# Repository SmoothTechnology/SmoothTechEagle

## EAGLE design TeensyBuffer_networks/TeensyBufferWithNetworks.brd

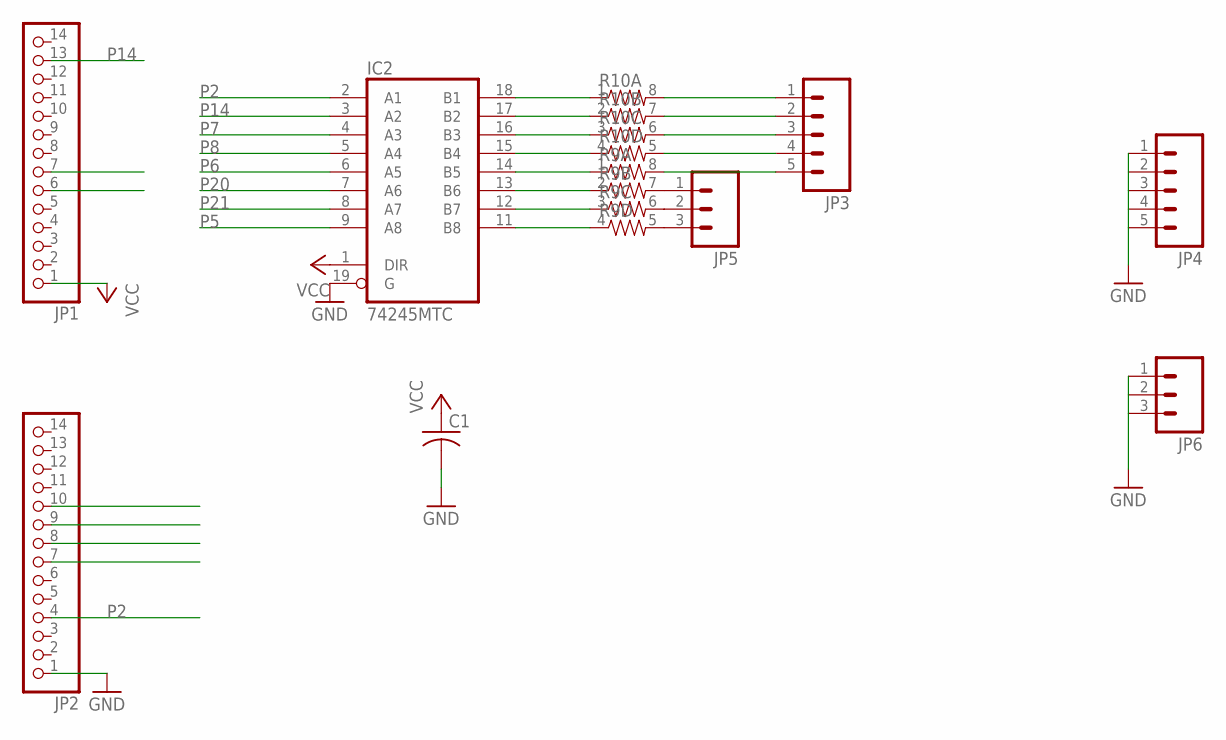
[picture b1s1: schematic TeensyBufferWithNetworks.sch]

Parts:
C1: C-USC0805; C0805
IC2: 74245MTC; SSOP20
JP1, JP2: PINHD-1X14-CB; 1X14-CB
JP3, JP4: M05NO_SILK; 1X05_NO_SILK
JP5, JP6: M031X03_NO_SILK; 1X03_NO_SILK
R9, R10: RESISTOR-ARRAY0603-ARV; 0603-ARV

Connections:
GND: C1.2, IC2.10 (GND), IC2.19 (G), JP2.1, JP4.1, JP4.2, JP4.3, JP4.4, JP4.5, JP6.1, JP6.2, JP6.3
unnamed: JP5.1, R9.7 (2)
unnamed: JP5.2, R9.6 (2)
unnamed: IC2.18 (B1), R10.1
unnamed: IC2.17 (B2), R10.2 (1)
unnamed: IC2.16 (B3), R10.3 (1)
unnamed: IC2.15 (B4), R10.4 (1)
unnamed: IC2.14 (B5), R9.1
unnamed: IC2.13 (B6), R9.2 (1)
unnamed: IC2.12 (B7), R9.3 (1)
unnamed: IC2.11 (B8), R9.4 (1)
unnamed: JP5.3, R9.5 (2)
unnamed: JP3.1, R10.8 (2)
unnamed: JP3.2, R10.7 (2)
unnamed: JP3.3, R10.6 (2)
unnamed: JP3.4, R10.5 (2)
unnamed: JP3.5, R9.8 (2)
P2: IC2.2 (A1), JP2.4
P5: IC2.9 (A8), JP2.7
P6: IC2.6 (A5), JP2.8
P7: IC2.4 (A3), JP2.9
P8: IC2.5 (A4), JP2.10
P14: IC2.3 (A2), JP1.13
P20: IC2.7 (A6), JP1.7
P21: IC2.8 (A7), JP1.6
VCC: C1.1, IC2.1 (DIR), IC2.20 (VCC), JP1.1

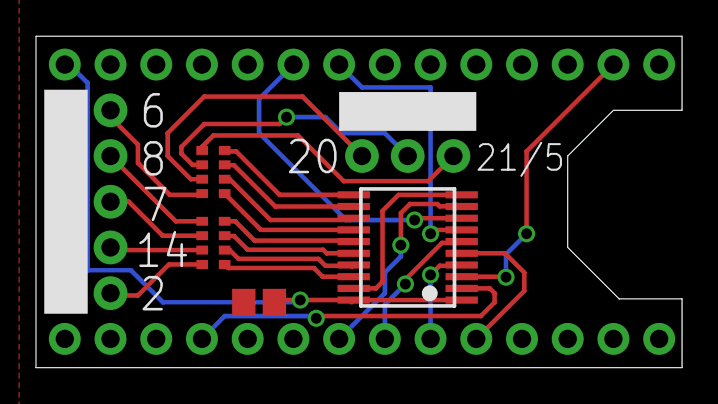
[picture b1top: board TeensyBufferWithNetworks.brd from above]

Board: 2 copper layers, 35.9 x 18.4 mm, 10 parts (0 on the bottom side), 26 nets.

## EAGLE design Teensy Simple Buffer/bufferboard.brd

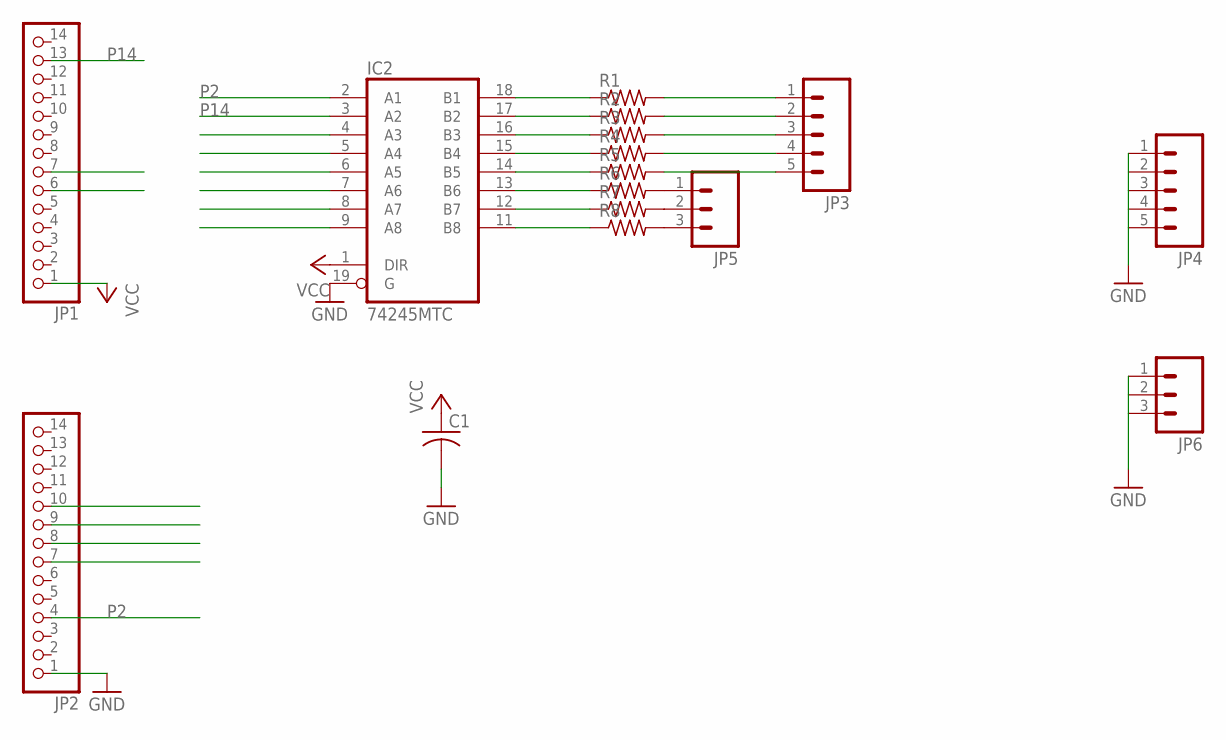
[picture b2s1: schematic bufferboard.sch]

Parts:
C1: C-USC0805; C0805
IC2: 74245MTC; SSOP20
JP1, JP2: PINHD-1X14-CB; 1X14-CB
JP3, JP4: M05NO_SILK; 1X05_NO_SILK
JP5, JP6: M031X03_NO_SILK; 1X03_NO_SILK
R1, R2, R3, R4, R5, R6, R7, R8: R-US_R0805; R0805

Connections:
GND: C1.2, IC2.10 (GND), IC2.19 (G), JP2.1, JP4.1, JP4.2, JP4.3, JP4.4, JP4.5, JP6.1, JP6.2, JP6.3
unnamed: JP5.1, R6.2
unnamed: JP5.2, R7.2
unnamed: IC2.18 (B1), R1.1
unnamed: IC2.17 (B2), R2.1
unnamed: IC2.16 (B3), R3.1
unnamed: IC2.15 (B4), R4.1
unnamed: IC2.14 (B5), R5.1
unnamed: IC2.13 (B6), R6.1
unnamed: IC2.12 (B7), R7.1
unnamed: IC2.11 (B8), R8.1
unnamed: JP5.3, R8.2
unnamed: JP3.1, R1.2
unnamed: JP3.2, R2.2
unnamed: JP3.3, R3.2
unnamed: JP3.4, R4.2
unnamed: JP3.5, R5.2
P2: IC2.2 (A1), JP2.4
P5: IC2.9 (A8), JP2.7
P6: IC2.6 (A5), JP2.8
P7: IC2.4 (A3), JP2.9
P8: IC2.5 (A4), JP2.10
P14: IC2.3 (A2), JP1.13
P20: IC2.7 (A6), JP1.7
P21: IC2.8 (A7), JP1.6
VCC: C1.1, IC2.1 (DIR), IC2.20 (VCC), JP1.1

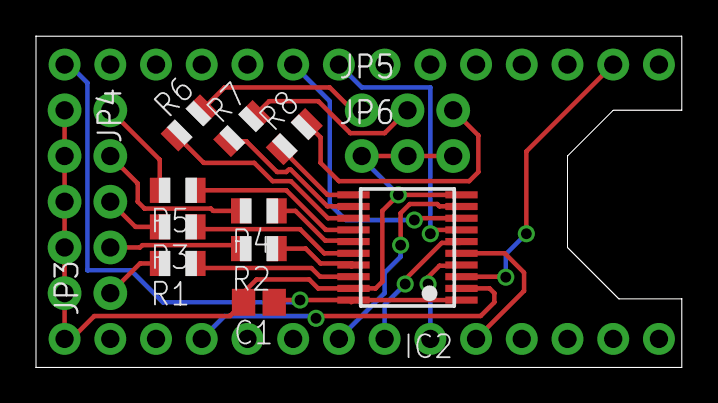
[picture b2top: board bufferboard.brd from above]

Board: 2 copper layers, 35.9 x 18.4 mm, 16 parts (0 on the bottom side), 26 nets.

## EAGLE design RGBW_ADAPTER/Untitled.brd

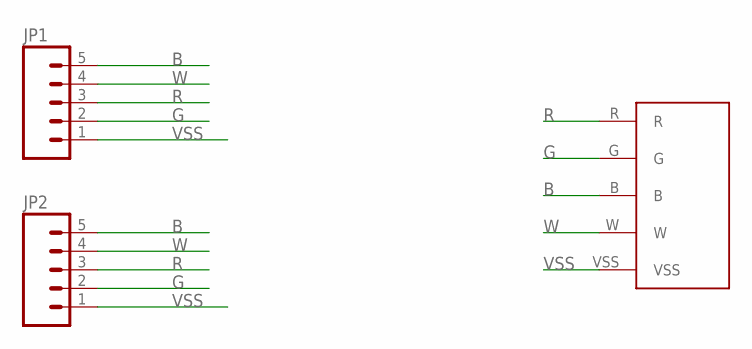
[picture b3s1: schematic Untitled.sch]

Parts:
JP1, JP2: M05PTH_LONGPADS; 1X05_LONGPADS
U$1: RGBWSTRIP

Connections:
B: JP1.5, JP2.5, U$1.B
G: JP1.2, JP2.2, U$1.G
R: JP1.3, JP2.3, U$1.R
VSS: JP1.1, JP2.1, U$1.VSS
W: JP1.4, JP2.4, U$1.W

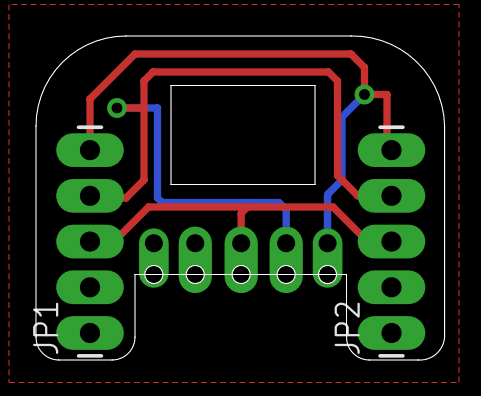
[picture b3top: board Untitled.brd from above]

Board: 2 copper layers, 22.7 x 18.0 mm, 3 parts (0 on the bottom side), 5 nets.

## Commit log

2016-11-30 added RGBW_adapter
2016-11-30 added logo
2016-11-30 added gerbers
2016-11-30 added real gerbers
2016-11-30 deleted old files
2016-11-30 realgerbs
2017-02-03 added teensy topper
2018-05-18 sync with james' local directory
2018-05-18 Added ETR Logo to lbr
2018-08-10 added part

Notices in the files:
parts and their libraries:
SparkFun-Connectors: Licensing: Creative Commons ShareAlike 4.0 International - https://creativecommons.org/licenses/by-sa/4.0
